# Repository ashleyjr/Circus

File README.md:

# Circus

## Installs

### Python 2.7
#### pip           
$ sudo apt-get install python-pip python-dev build-essential      

$ sudo pip install --upgrade pip 

$ sudo pip install --upgrade virtualenv 

$ sudo apt-get install python-tk    

### matplotlib     
$ sudo pip install matplotlib

### 8051
SDCC

SimplicityStudio

### Schematic capture/layout
#### KiCad
$sudo add-apt-repository --yes ppa:js-reynaud/kicad-4

$sudo apt update

$sudo apt install kicad

### Docs
$ sudo apt-get install texlive-latex-base

$ sudo apt-get install texlive-latex-extra

### GUI
$ sudo apt-get install libgtk-3-dev

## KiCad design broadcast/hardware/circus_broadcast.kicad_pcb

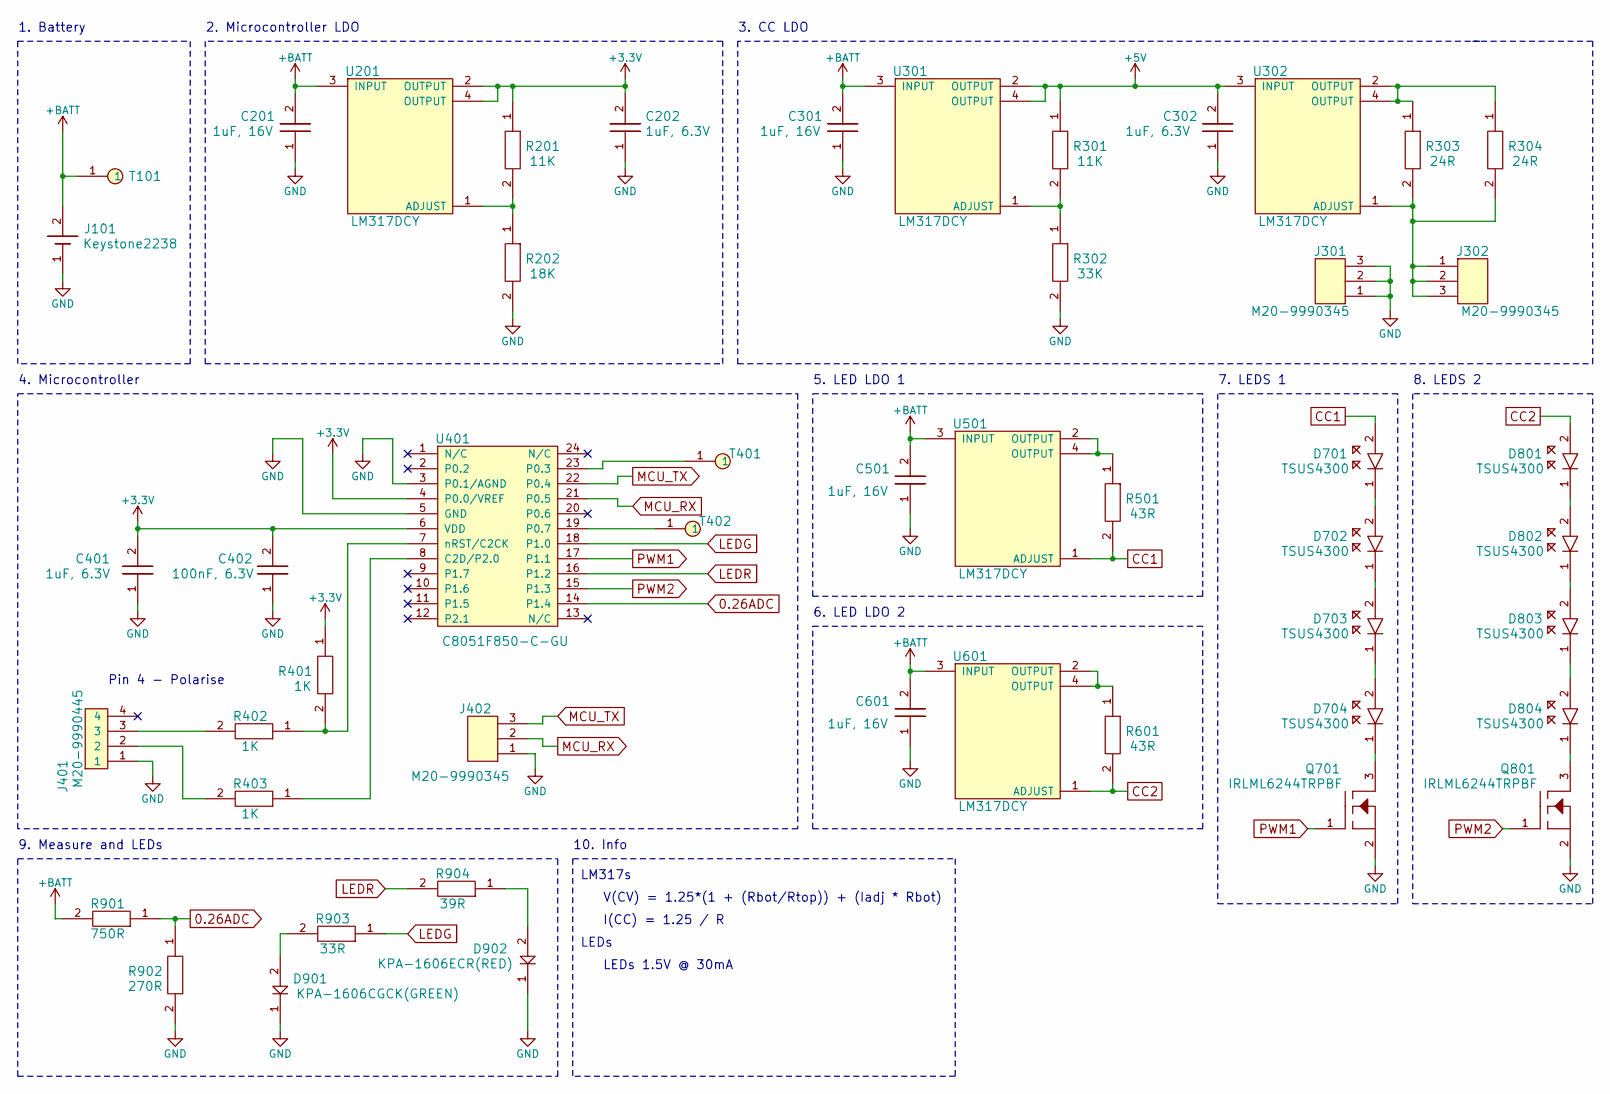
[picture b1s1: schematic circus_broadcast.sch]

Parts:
C201, C301, C501, C601: 1uF, 16V; 0603
C202, C302, C401: 1uF, 6.3V; 0603
C402: 100nF, 6.3V; 0402
D701, D702, D703, D704, D801, D802, D803, D804: TSUS4300
D901: KPA-1606CGCK(GREEN); KPA
D902: KPA-1606ECR(RED); KPA
J101: Keystone2238
J301, J302, J402: M20-9990345
J401: M20-9990445
Q701, Q801: IRLML6244TRPBF
R201, R301: 11K; 0402
R202: 18K; 0402
R302: 33K; 0402
R303, R304: 24R; 0402
R401, R402, R403: 1K; 0402
R501, R601: 43R; 0402
R901: 750R; 0402
R902: 270R; 0402
R903: 33R; 0402
R904: 39R; 0402
T101, T401, T402: TestPoint
U201, U301, U302, U501, U601: LM317DCY
U401: C8051F850-C-GU

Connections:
0.26ADC: R901.1, R902.1, U401.14 (P1.4)
+3V3: C202.2, C401.2, C402.2, R201.1, R401.1, U201.2 (OUTPUT), U201.4 (OUTPUT), U401.4 (P0.0/VREF), U401.6 (VDD)
+5V: C302.2, R301.1, U301.2 (OUTPUT), U301.4 (OUTPUT), U302.3 (INPUT)
+BATT: C201.2, C301.2, C501.2, C601.2, J101.2, R901.2, T101.1, U201.3 (INPUT), U301.3 (INPUT), U501.3 (INPUT), U601.3 (INPUT)
CC1: D701.2, R501.2, U501.1 (ADJUST)
CC2: D801.2, R601.2, U601.1 (ADJUST)
GND: C201.1, C202.1, C301.1, C302.1, C401.1, C402.1, C501.1, C601.1, D901.1, D902.1, J101.1, J301.1, J301.2, J301.3, J401.1, J402.1, Q701.2, Q801.2, R202.2, R302.2, R902.2, U401.3 (P0.1/AGND), U401.5 (GND)
LEDG: R903.1, U401.18 (P1.0)
LEDR: R904.2, U401.16 (P1.2)
MCU_RX: J402.2, U401.21 (P0.5)
MCU_TX: J402.3, U401.22 (P0.4)
unnamed: D701.1, D702.2
unnamed: D702.1, D703.2
unnamed: D703.1, D704.2
unnamed: D704.1, Q701.3
unnamed: D801.1, D802.2
unnamed: D802.1, D803.2
unnamed: D803.1, D804.2
unnamed: D804.1, Q801.3
unnamed: D901.2, R903.2
unnamed: D902.2, R904.1
unnamed: J302.1, J302.2, J302.3, R303.2, R304.2, U302.1 (ADJUST)
unnamed: J401.2, R403.2
unnamed: J401.3, R402.2
unnamed: R201.2, R202.1, U201.1 (ADJUST)
unnamed: R301.2, R302.1, U301.1 (ADJUST)
unnamed: R303.1, R304.1, U302.2 (OUTPUT), U302.4 (OUTPUT)
unnamed: R401.2, R402.1, U401.7 (nRST/C2CK)
unnamed: R403.1, U401.8 (C2D/P2.0)
unnamed: R501.1, U501.2 (OUTPUT), U501.4 (OUTPUT)
unnamed: R601.1, U601.2 (OUTPUT), U601.4 (OUTPUT)
unnamed: T401.1, U401.23 (P0.3)
unnamed: T402.1, U401.19 (P0.7)
PWM1: Q701.1, U401.17 (P1.1)
PWM2: Q801.1, U401.15 (P1.3)

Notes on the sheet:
Pin 4 - Polarise
1. Battery
2. Microcontroller LDO
3. CC LDO
4. Microcontroller
V(CV) = 1.25*(1 + (Rbot/Rtop)) + (Iadj * Rbot)
I(CC) = 1.25 / R
LEDs 1.5V @ 30mA
5. LED LDO 1
6. LED LDO 2
7. LEDS 1
8. LEDS 2
LM317s
LEDs
10. Info
9. Measure and LEDs

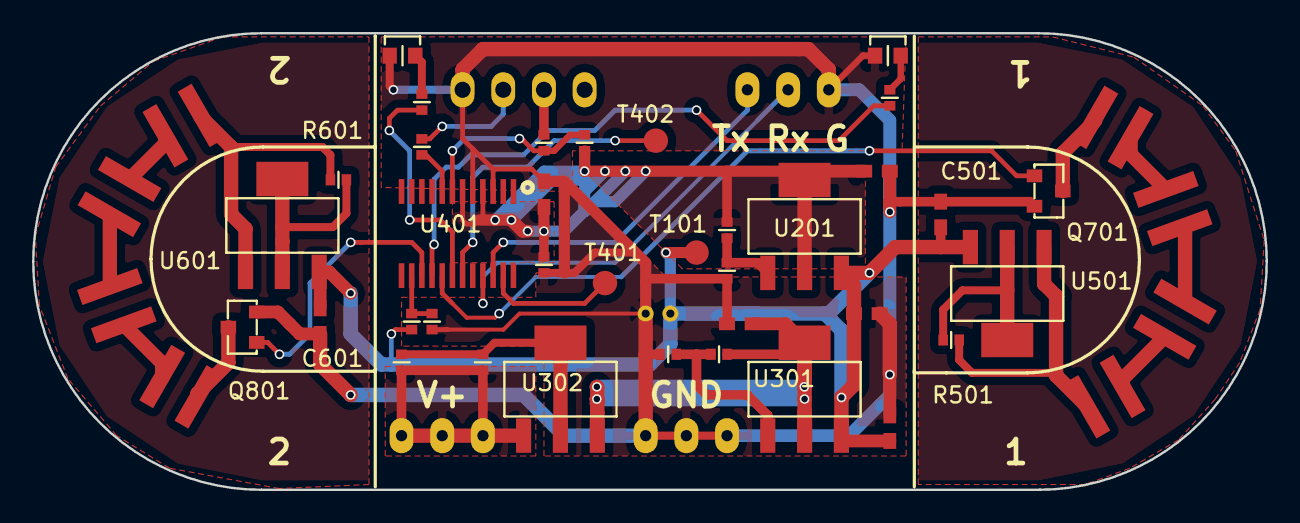
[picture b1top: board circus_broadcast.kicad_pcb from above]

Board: 2 copper layers, 77.0 x 28.5 mm, 49 parts (0 on the bottom side), 35 nets.

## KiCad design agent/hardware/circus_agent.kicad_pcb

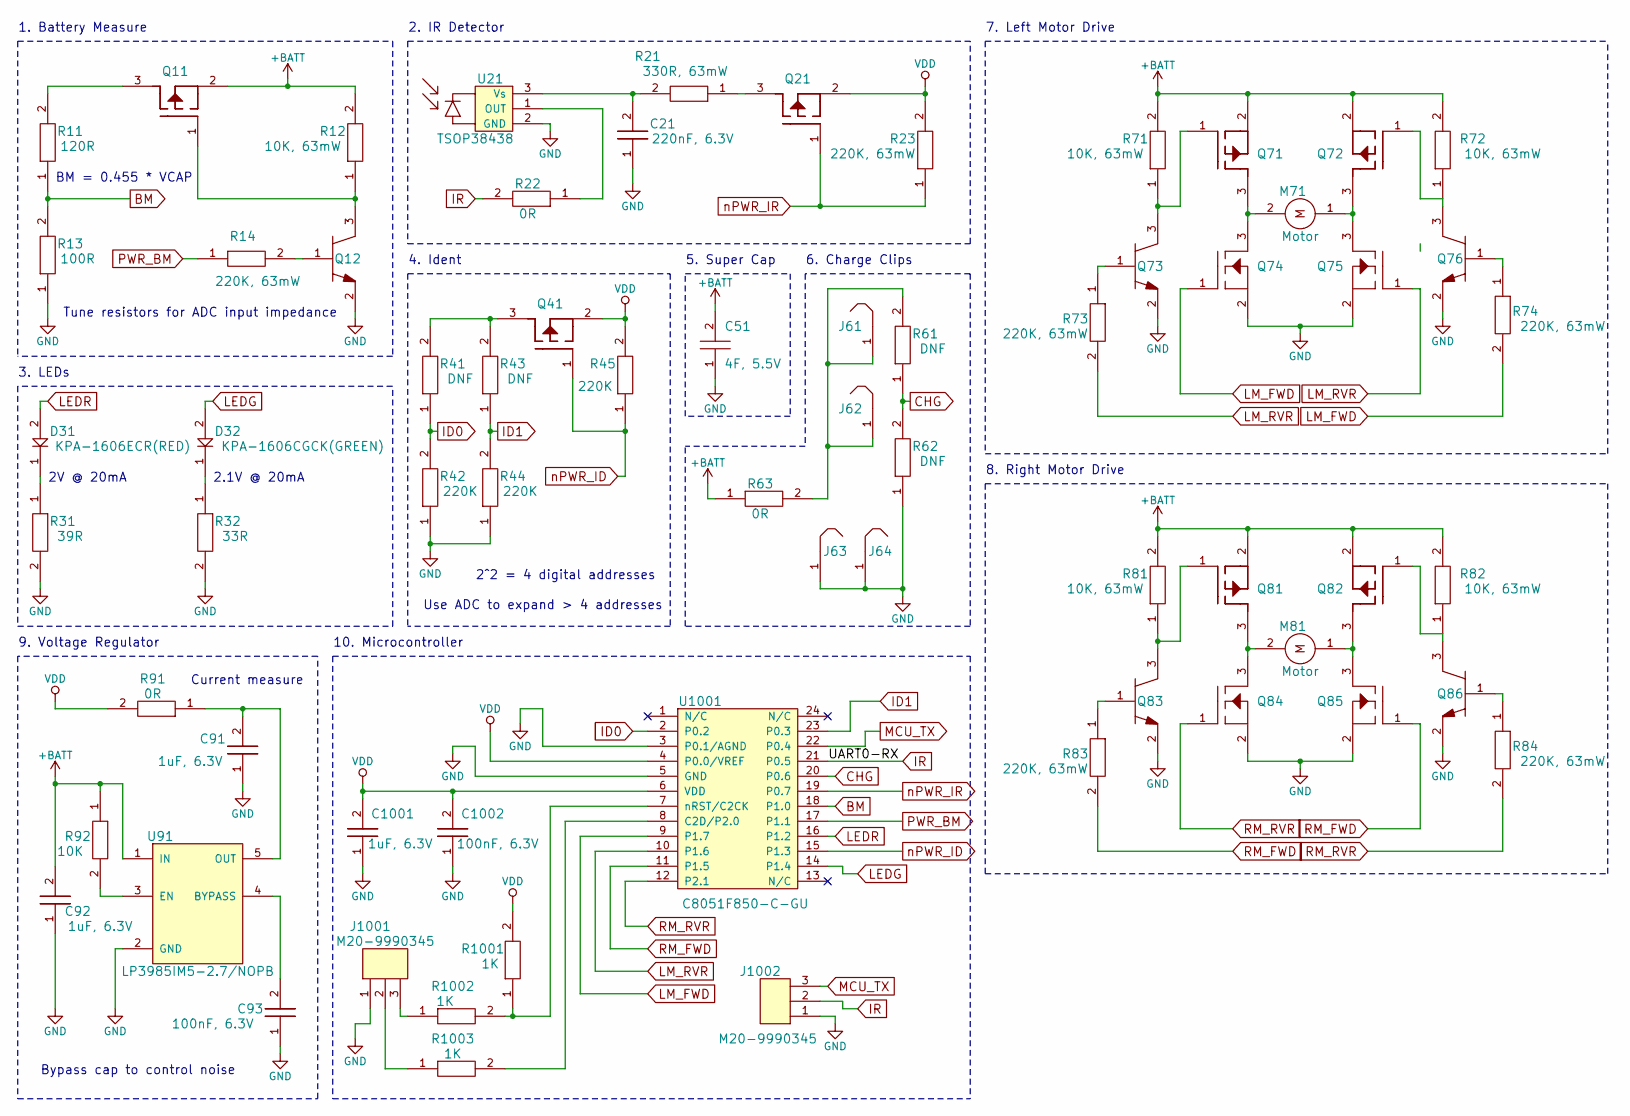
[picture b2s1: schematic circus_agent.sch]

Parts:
C21: 220nF, 6.3V; 0402; PartNum MC0402X224K6R3CT
C51: 4F, 5.5V; SuperCap
C91, C92, C1001: 1uF, 6.3V; 0402; PartNum MC0402X224K6R3CT
C93, C1002: 100nF, 6.3V; 0402; PartNum MC0402X224K6R3CT
D31: KPA-1606ECR(RED); KPA
D32: KPA-1606CGCK(GREEN); KPA
J61, J62, J63, J64: PowerClip
J1001, J1002: M20-9990345
M71, M81: Motor
Q11, Q21, Q41, Q71, Q72, Q81, Q82: PMV65XPEA; PartNum PMV65XPEA
Q12, Q73, Q76, Q83, Q86: MMBT2222LT1G
Q74, Q75, Q84, Q85: IRLML6244TRPBF
R11: 120R; 0402; PartNum MCMR04X4701FTL
R12, R71, R72, R81, R82: 10K, 63mW; 0402; PartNum MCMR04X4701FTL
R13: 100R; 0402; PartNum MCMR04X4701FTL
R14, R23, R73, R74, R83, R84: 220K, 63mW; 0402; PartNum MCMR04X4701FTL
R21: 330R, 63mW; 0402; PartNum CRCW0402330RFKED
R22, R63, R91: 0R; 0402; PartNum MCMR04X4701FTL
R31: 39R; 0402; PartNum MCMR04X4701FTL
R32: 33R; 0402; PartNum MCMR04X4701FTL
R41, R43, R61, R62: DNF; 0402; PartNum MCMR04X4701FTL
R42, R44, R45: 220K; 0402; PartNum MCMR04X4701FTL
R92: 10K; 0402; PartNum MCMR04X4701FTL
R1001, R1002, R1003: 1K; 0402; PartNum MCMR04X4701FTL
U21: TSOP38438
U91: LP3985IM5-2.7/NOPB; LP3985
U1001: C8051F850-C-GU

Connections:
+BATT: C51.2, C92.2, Q11.2, Q71.2, Q72.2, Q81.2, Q82.2, R12.2, R63.1, R71.2, R72.2, R81.2, R82.2, R92.1, U91.1 (IN)
BM: R11.1, R13.2, U1001.18 (P1.0)
CHG: R61.1, R62.2, U1001.20 (P0.6)
GND: C21.1, C51.1, C91.1, C92.1, C93.1, C1001.1, C1002.1, J63.1, J64.1, J1001.1, J1002.1, Q12.2, Q73.2, Q74.2, Q75.2, Q76.2, Q83.2, Q84.2, Q85.2, Q86.2, R13.1, R31.2, R32.2, R42.1, R44.1, R62.1, U21.2 (GND), U91.2 (GND), U1001.3 (P0.1/AGND), U1001.5 (GND)
ID0: R41.1, R42.2, U1001.2 (P0.2)
ID1: R43.1, R44.2, U1001.23 (P0.3)
IR: J1002.2, R22.2, U1001.21 (P0.5)
LEDG: D32.2, U1001.14 (P1.4)
LEDR: D31.2, U1001.16 (P1.2)
LM_FWD: Q74.1, R74.2, U1001.9 (P1.7)
LM_RVR: Q75.1, R73.2, U1001.10 (P1.6)
MCU_TX: J1002.3, U1001.22 (P0.4)
unnamed: C21.2, R21.2, U21.3 (Vs)
unnamed: C91.2, R91.1, U91.5 (OUT)
unnamed: C93.2, U91.4 (BYPASS)
unnamed: D31.1, R31.1
unnamed: D32.1, R32.1
unnamed: J61.1, J62.1, R61.2, R63.2
unnamed: J1001.2, R1003.1
unnamed: J1001.3, R1002.1
unnamed: M71.1, Q72.3, Q75.3
unnamed: M71.2, Q71.3, Q74.3
unnamed: M81.1, Q82.3, Q85.3
unnamed: M81.2, Q81.3, Q84.3
unnamed: Q11.1, Q12.3, R12.1
unnamed: Q11.3, R11.2
unnamed: Q12.1, R14.2
unnamed: Q21.3, R21.1
unnamed: Q41.3, R41.2, R43.2
unnamed: Q71.1, Q73.3, R71.1
unnamed: Q72.1, Q76.3, R72.1
unnamed: Q73.1, R73.1
unnamed: Q76.1, R74.1
unnamed: Q81.1, Q83.3, R81.1
unnamed: Q82.1, Q86.3, R82.1
unnamed: Q83.1, R83.1
unnamed: Q86.1, R84.1
unnamed: R22.1, U21.1 (OUT)
unnamed: R92.2, U91.3 (EN)
unnamed: R1001.1, R1002.2, U1001.7 (nRST/C2CK)
unnamed: R1003.2, U1001.8 (C2D/P2.0)
PWR_BM: R14.1, U1001.17 (P1.1)
RM_FWD: Q85.1, R83.2, U1001.11 (P1.5)
RM_RVR: Q84.1, R84.2, U1001.12 (P2.1)
VDD: C1001.2, C1002.2, Q21.2, Q41.2, R23.2, R45.2, R91.2, R1001.2, U1001.4 (P0.0/VREF), U1001.6 (VDD)
nPWR_ID: Q41.1, R45.1, U1001.15 (P1.3)
nPWR_IR: Q21.1, R23.1, U1001.19 (P0.7)

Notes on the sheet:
7. Left Motor Drive
8. Right Motor Drive
2. IR Detector
4. Ident
1. Battery Measure
10. Microcontroller
3. LEDs
5. Super Cap
2V @ 20mA
2.1V @ 20mA
9. Voltage Regulator
Bypass cap to control noise
2^2 = 4 digital addresses
Use ADC to expand > 4 addresses
Current measure
6. Charge Clips
BM = 0.455 * VCAP
Tune resistors for ADC input impedance

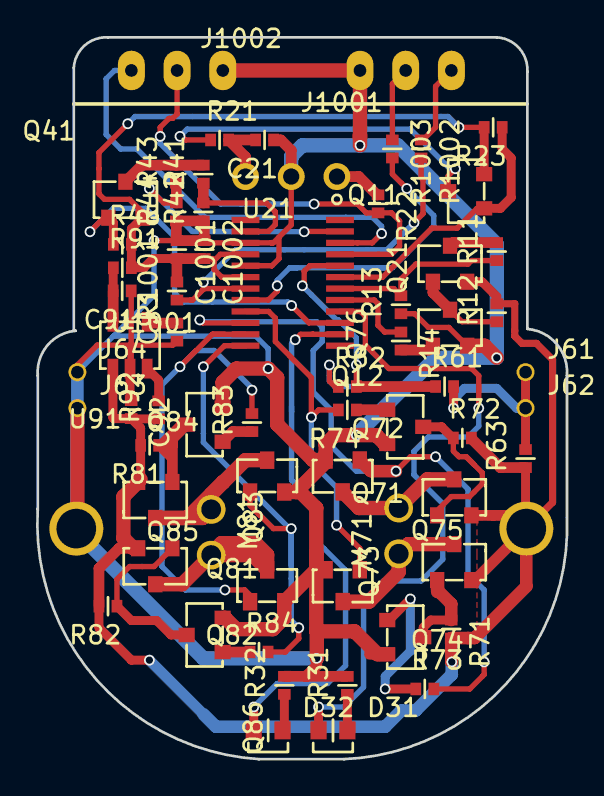
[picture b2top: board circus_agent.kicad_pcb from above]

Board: 2 copper layers, 29.4 x 40.1 mm, 66 parts (1 on the bottom side), 47 nets.

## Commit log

2018-06-24 copy over c files from Switcher
2018-06-24 update readme and cap info
2018-06-25 ordered some parts to experiment
2018-06-26 Add datasheet, schs for ir and mcu
2018-06-26 added highside switch
2018-06-27 Added supercap and power rails
2018-06-27 Added h bridge and nmos
2018-06-28 Added BJT for highsides
2018-06-28 add battery measure and ID
2018-06-29 add pdfs and synbols for leds and prog
2018-06-30 added the pinout, LDO
2018-07-01 Duel drive with LEDs and ID. Added header
2018-07-04 designators and pass erc
2018-07-10 temp footprint and charge detection
2018-07-14 ADC and timer driven software pwm working on card
2018-07-14 Added IR footprint
2018-07-14 more footprints
2018-07-14 Motor, cap footprints and remove reverse fet
2018-07-14 updated power rails
2018-07-14 first stab at layout
2018-07-15 First outline for PCB
2018-07-15 adjust outline
2018-07-15 Added 3d model
2018-07-18 Opt PCB layout and adjust drc
2018-07-19 More layout opt and Rev A marking
2018-07-20 final route opt
2018-07-22 Generate gerbers
2018-07-23 flash script and TEST UART
2018-07-24 Added buffering functions
2018-07-29 Started spec
2018-07-30 Updates to spec on comms time outs
2018-07-31 Added time diagram for carrier
2018-08-03 Added cmd table and diagram for SM agent
2018-08-04 Added spec lines on the GUI
2018-08-04 Start quick GUI in GTK
2018-08-05 Added set and clear button to GUI
2018-08-07 Added timer for buffer
2018-08-09 add uart writer
2018-08-14 new serial interface
2018-08-14 broadcast output of carrier
2018-08-14 clean up main for broadcast
2018-08-23 Fixes #3
2018-08-24 LED/opamp data sheets and started capture
2018-09-16 started build log
2018-09-30 sw pwm working with motors
2018-10-01 Added LM317 to broadcast
2018-10-02 exported pdf
2018-10-02 Added mcu circuit and format
2018-10-08 Added designators and values
2018-10-16 Added ADC, LEDS and passes erc
2018-10-18 Associate, footprint and start placement
2018-10-21 MOre lyaout
2018-11-05 All all footprints and made 0.1 inch headers bigger
2018-11-07 First passing layout
2018-11-08 tidy routing
2018-11-09 Final layout
2018-11-09 Remove copper text
2018-11-09 Export gerbers
2018-12-11 Order placed
2019-01-13 UART working over IR at 1200 baud
